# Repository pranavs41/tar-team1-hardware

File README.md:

# TAR Team 1 Hardware

Hardware for the Team 1 swarm mapping project (Texas Aerial Robotics, UT Austin).

## Start here

- **Wiring something to the board, or writing firmware for it:** [`docs/hardware-reference.md`](docs/hardware-reference.md) has every connector, pin, voltage and limit on one page.
- **Reading the schematic without KiCad:** [`schematics/network-drone-fc-schematic.pdf`](schematics/network-drone-fc-schematic.pdf).
- **Designing the frame around the board:** [`cad/network-drone-fc.step`](cad/network-drone-fc.step) is the assembled board as a 3D part.
- **Who is doing what:** [`TASKS.md`](TASKS.md) lists each person's tasks and where their work meets someone else's.
- **What one drone is made of and costs:** [`docs/parts-list.md`](docs/parts-list.md) has every part with its maker, a US or European seller, the price, and the total.

## Repository layout

```
TASKS.md                who owns what, task checklists, the charging concept
pcb/
  network-drone-fc/     KiCad 9 project: the board and the schematic source
    lib/                custom symbols, footprints, 3D models
    production/         gerbers, BOM and notes per board revision
  ground-station/       the ground station's power and main boards (schematics from Python block files)
schematics/             the schematic as a PDF
cad/                    board 3D model (STEP), board pictures, frame CAD
docs/
  hardware-reference.md every connector, pin, voltage and limit on one page
  parts-list.md         every part: maker, seller, price, stock problems, total cost
  charging-board.md     the charging board: plan, parts, and its 7-pin link to the flight controller
  pcb-test-plan.md      how the board gets checked: before ordering, on the bench, in flight
  frame-test-plan.md    load, drop and vibration tests for the printed frame
  DESIGN.md             design doc: requirements, block diagram, parts, power, layout
  circuits/             how every circuit works and why it's there, box by box
  pin-map.md            ESP32 pin, net name and destination, for firmware
  power-budget.md       current per rail, regulator heat, copper and sag check
  bring-up.md           first power-on checklist
  design-decisions.md   dated log of design decisions
  datasheets.md         links to every datasheet and reference design
tools/
  power_budget.py       the model behind power-budget.md
```

KiCad keeps a project's schematic and board in one folder, so both source files are in `pcb/`. The `schematics/` folder holds the readable PDF.

## Network drone flight controller

KiCad 9 project in [`pcb/network-drone-fc/`](pcb/network-drone-fc/). Open `network-drone-fc.kicad_pro`. The design plan is in [`docs/DESIGN.md`](docs/DESIGN.md).

[View the schematic as a PDF](schematics/network-drone-fc-schematic.pdf) or the board pictures in [`cad/`](cad/) if you don't have KiCad. Regenerate the PDF after schematic changes, from the project folder: `kicad-cli sch export pdf network-drone-fc.kicad_sch -o ../../schematics/network-drone-fc-schematic.pdf`.

- 4-layer board, 36 × 39 mm, four 3.2 mm M3 holes on a 20 × 20 mm pattern so it stacks on a bought 20 × 20 4-in-1 ESC
- Two cable ports for off-board parts: J5 carries 5 V and I2C to the TF-Luna obstacle sensor at the front of the drone, J6 carries 5 V and a UART to the VoCore2 networking module
- All parts on the top side except C35, the bulk capacitor on the bottom, so the top can be reflowed on a hot plate and C35 soldered after with an iron; test points (bare pads) are on the bottom
- Designed for a 2S battery only

Where to buy every part, with prices and each maker's country, is in [`docs/parts-list.md`](docs/parts-list.md). The LCSC numbers in the table below are where the KiCad symbols and footprints were imported from; LCSC is a Chinese distributor, and the parts list gives a DigiKey source for each one.

### Parts in `lib/tar_fc`

Symbols, footprints and 3D models (STEP) pulled from LCSC/EasyEDA. The project's library tables already point at them.

| Function | Part | LCSC |
|---|---|---|
| MCU, bare chip (8 MB flash in package) | ESP32-S3FN8 | C2913196 |
| MCU crystal, 40 MHz ±10 ppm | Q22FA12800101 (2016) | C255898 |
| MCU module (fallback only, not used) | ESP32-S3-MINI-1U-N8 | C2980299 |
| Flight IMU (SPI) | ICM-42688-P | C1850418 |
| Barometer | BMP581 | C5362283 |
| GPS | u-blox MAX-M10S | C4153167 |
| Antenna connector (ESP32 / GPS) | U.FL-R-SMT-1 | C88374 |
| 5 V buck (3.8 to 32 V in) | AP63205WU-7 | C2071056 |
| 3.3 V LDO, digital (WSON-6 with thermal pad) | TLV75733PDRVR | C2868428 |
| 3.3 V LDO, sensors (low noise) | TPS7A2033PDBVR | C2862740 |
| Battery TVS (12 V standoff, 2S only) | SMAJ12A | |
| GPS bias-T inductor, 27 nH (fit only for an active antenna) | Murata LQG15HS27NJ02D (0402) | C12669 |
| USB 5 V OR-ing diode | B5819W | C8598 |
| USB ESD | USBLC6-2SC6 | C7519 |
| USB-C (USB 2.0, 16-pin) | TYPE-C 16PIN 2MD(073) | C2765186 |
| ESC connector (8-pin JST-SH) | SM08B-SRSS-TB | C160407 |
| Radio port J6 (4-pin JST-SH, top entry) | BM04B-SRSS-TB | C160390 |
| Bulk capacitor on VBAT (C35, bottom side) | Kyocera AVX TCJD107M025R0055E, 100 µF 25 V polymer tantalum, D case | C2159920 |
| Battery capacitor on the ESC's pads, not on this board | 470 µF 35 V low-ESR electrolytic (any of the ones sold for FPV ESCs) | per build |
| Peripheral port (4-pin JST-GH) | SM04B-GHS-TB (LCSC stock low; drop-in alt XY-SM04B-GHS-TB C51940118) | C189895 |
| VDD3P3 filter inductor, 2.0 nH ±0.1 nH, 900 mA | Murata LQG15HS2N0B02D (0402) | C2986275 |

From the stock KiCad libraries (already have 3D models):

- Passives: `Resistor_SMD` / `Capacitor_SMD` 0402
- Buck inductor, 4.7 µH: `Inductor_SMD:L_1008_2520Metric`. It must have a saturation current of 2 A or more now that the sensor and radio ports draw from the 5 V rail; the FTC252010S4R7MBCA (C5832360) listed earlier saturates near 1.1 A and is no longer enough. Check the value against the AP63205 datasheet.
- 6-pin JST-GH: `Connector_JST:JST_GH_SM06B-GHS-TB_1x06-1MP_P1.25mm_Horizontal`
- Mounting holes: `MountingHole:MountingHole_3.2mm_M3` (plain, no copper, courtyard trimmed to the 3 mm keep-out)
- RESET/BOOT pad pairs: `Jumper:SolderJumper-2_P1.3mm_Open_RoundedPad1.0x1.5mm`

### Adding a part

```
pip install easyeda2kicad
python -m easyeda2kicad --full --lcsc_id=C123456 --output pcb/network-drone-fc/lib/tar_fc
```

Then change the new footprint's `model` path to `${KIPRJMOD}/lib/tar_fc.3dshapes/<name>.step` so it works on every machine.

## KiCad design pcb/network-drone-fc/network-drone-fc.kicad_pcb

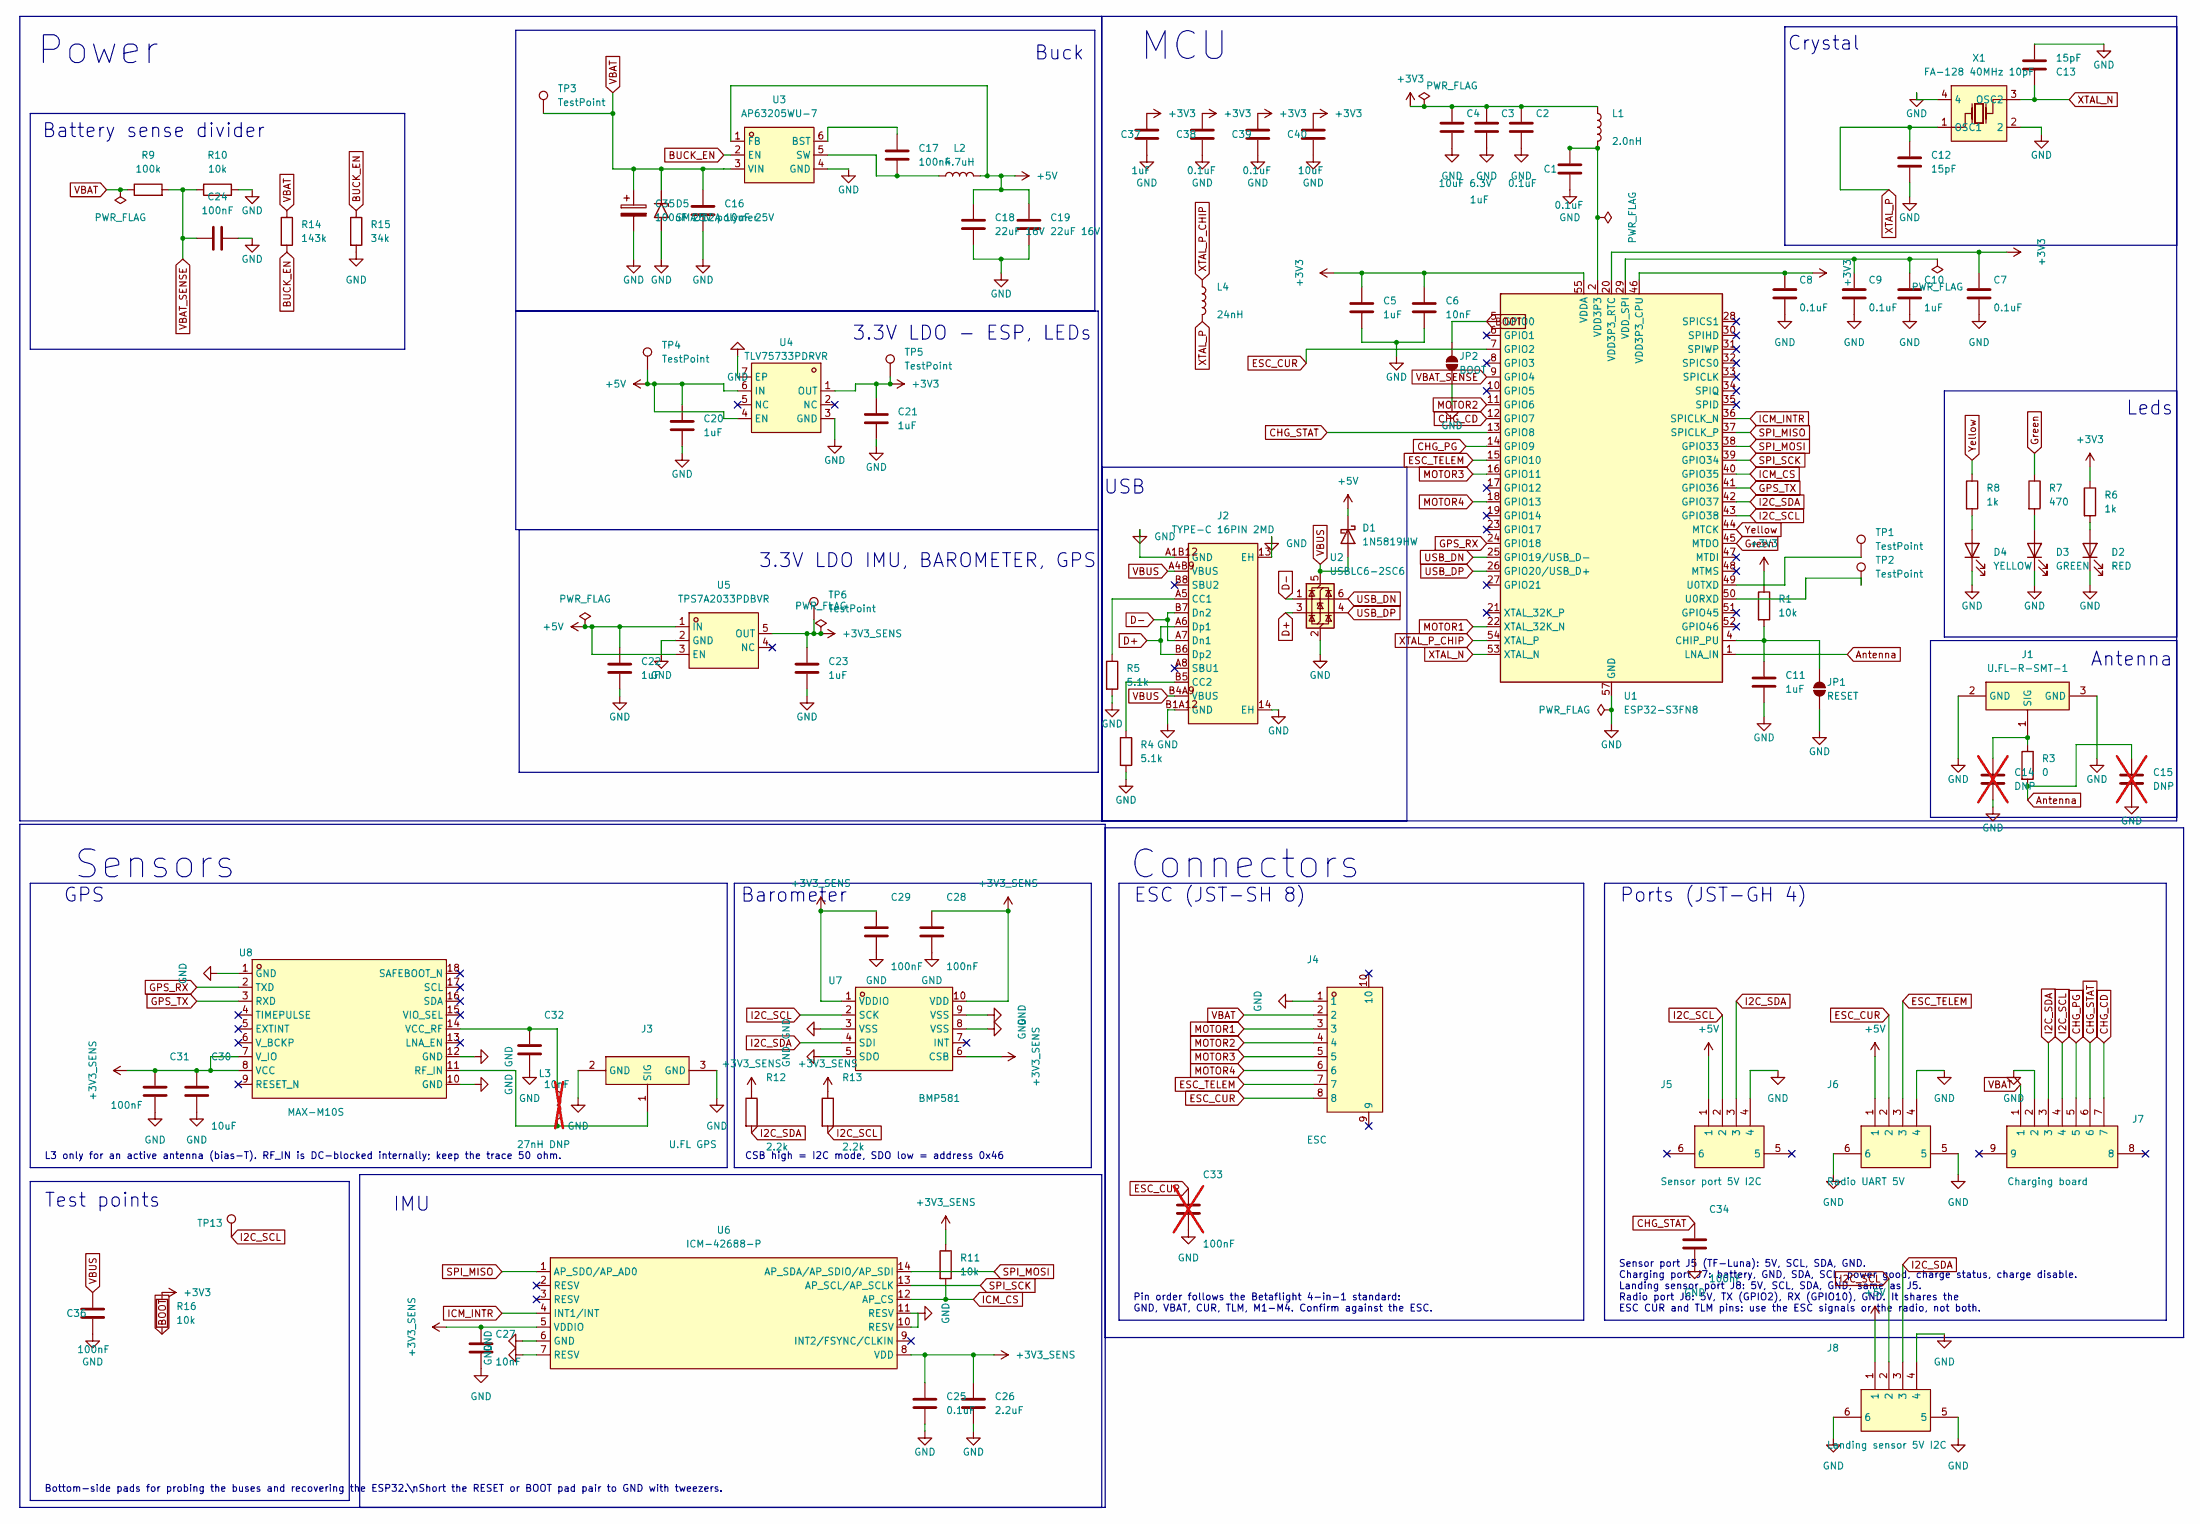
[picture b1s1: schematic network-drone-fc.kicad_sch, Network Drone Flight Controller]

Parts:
C1, C2, C7, C8, C9, C25, C38, C39: 0.1uF; C_0402_1005Metric
C3, C5, C10, C11, C20, C21, C22, C23, C37: 1uF; C_0402_1005Metric
C4: 10uF 6.3V; C_0603_1608Metric
C6, C27, C32: 10nF; C_0402_1005Metric
C12, C13: 15pF; C_0402_1005Metric
C14, C15: DNP; C_0402_1005Metric; not fitted
C16: 10uF 25V; C_0805_2012Metric
C17, C24, C28, C29, C31, C34, C36: 100nF; C_0402_1005Metric
C18, C19: 22uF 16V; C_0805_2012Metric
C26: 2.2uF; C_0402_1005Metric
C30, C40: 10uF; C_0603_1608Metric
C33: 100nF; C_0402_1005Metric; not fitted
C35: 100uF 25V polymer; CP_EIA-7343-31_Kemet-D_HandSolder
D1: 1N5819HW; D_SOD-123
D2: RED; LED_0603_1608Metric
D3: GREEN; LED_0603_1608Metric
D4: YELLOW; LED_0603_1608Metric
D5: SMAJ12A; SMA_L4.4-W2.6-LS5.0-RD
J1: U.FL-R-SMT-1; RF-SMD_FRF05002-JSS103M; MPN U.FL-R-SMT-1(80); LCSC Part C88374
J2: TYPE-C 16PIN 2MD; USB-C-SMD_TYPE-C-16PIN-2MD-073; MPN TYPE-C 16PIN 2MD(073); LCSC Part C2765186
J3: U.FL GPS; RF-SMD_FRF05002-JSS103M; LCSC C88374
J4: ESC; CONN-TH_SM08B-SRSS-TB-LF-SN; LCSC C160407
J5: Sensor port 5V I2C; CONN-SMD_4P-P1.25_SM04B-GHS-TB-LF-SN; LCSC C189895
J6: Radio UART 5V; JST_SH_BM04B-SRSS-TB_1x04_Vertical; LCSC C189895
J7: Charging board; JST_SH_SM07B-SRSS-TB_1x07_Horizontal
J8: Landing sensor 5V I2C; JST_SH_BM04B-SRSS-TB_1x04_Vertical; LCSC C189895
JP1: RESET; SolderJumper-2_P1.3mm_Open_RoundedPad1.0x1.5mm
JP2: BOOT; SolderJumper-2_P1.3mm_Open_RoundedPad1.0x1.5mm
L1: 2.0nH; L_0402_1005Metric
L2: 4.7uH; L_1008_2520Metric
L3: 27nH DNP; L_0402_1005Metric; not fitted
L4: 24nH; L_0402_1005Metric
R1, R10, R11, R16: 10k; R_0402_1005Metric
R3: 0; R_0402_1005Metric
R4, R5: 5.1k; R_0402_1005Metric
R6, R8: 1k; R_0402_1005Metric
R7: 470; R_0402_1005Metric
R9: 100k; R_0402_1005Metric
R12, R13: 2.2k; R_0402_1005Metric
R14: 143k; R_0402_1005Metric
R15: 34k; R_0402_1005Metric
TP1, TP2, TP3, TP4, TP5, TP6, TP13: TestPoint; TestPoint_Pad_D1.0mm
U1: ESP32-S3FN8; QFN-56-1EP_7x7mm_P0.4mm_EP4x4mm
U2: USBLC6-2SC6; SOT-23-6
U3: AP63205WU-7; TSOT-23-6_L2.9-W1.6-P0.95-LS2.8-BL; MPN AP63205WU-7; LCSC Part C2071056
U4: TLV75733PDRVR; TDFN-6_L2.0-W2.0-P0.65-TL-EP; MPN TLV75733PDRVR; LCSC Part C485517
U5: TPS7A2033PDBVR; SOT-23-5_L2.9-W1.6-P0.95-LS2.8-BR; MPN TPS7A2033PDBVR; LCSC Part C2862740
U6: ICM-42688-P; LGA-14_L3.0-W2.5-P0.50-TL; MPN ICM-42688-P; LCSC Part C1850418
U7: BMP581; LGA-10_L2.0-W2.0-P0.50-TL_BMP581; LCSC C5362283
U8: MAX-M10S; SMD-18_L10.1-W9.7-P1.10-TL_SKG09F; LCSC C4153167
X1: FA-128 40MHz 10pF; CRYSTAL-SMD_4P-L2.0-W1.6-BL; MPN Q22FA12800101; LCSC Part C255898

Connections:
+3V3: C2.1, C3.1, C4.1, C5.1, C6.1, C7.1, C8.1, C21.1, C37.1, C38.1, C39.1, C40.1, L1.1, R1.1, R6.1, R16.1, TP5.1, U1.20 (VDD3P3_RTC), U1.46 (VDD3P3_CPU), U1.55 (VDDA), U1.56 (VDDA), U4.1 (OUT)
+3V3_SENS: C23.1, C25.1, C26.2, C27.1, C28.1, C29.1, C30.1, C31.1, R11.1, R12.1, R13.1, TP6.1, U5.5 (OUT), U6.5 (VDDIO), U6.8 (VDD), U7.1 (VDDIO), U7.6 (CSB), U7.10 (VDD), U8.7 (V_IO), U8.8 (VCC)
Antenna: C15.1, R3.2, U1.1 (LNA_IN)
BOOT: JP2.2 (B), R16.2, U1.5 (GPIO0)
BUCK_EN: R14.2, R15.1, U3.2 (EN)
CHG_CD: J7.7, U1.12 (GPIO7)
CHG_PG: J7.5, U1.14 (GPIO9)
CHG_STAT: C34.1, J7.6, U1.13 (GPIO8)
D+: J2.A6 (Dp1), J2.B6 (Dp2), U2.3 (I/O2)
D-: J2.A7 (Dn1), J2.B7 (Dn2), U2.1 (I/O1)
ESC_CUR: C33.1, J4.8, J6.2, U1.7 (GPIO2)
ESC_TELEM: J4.7, J6.3, U1.15 (GPIO10)
GPS_RX: U1.24 (GPIO18), U8.2 (TXD)
GPS_TX: U1.41 (GPIO36), U8.3 (RXD)
Green: R7.1, U1.45 (MTDO)
I2C_SCL: J5.2, J7.4, J8.2, R13.2, TP13.1, U1.43 (GPIO38), U7.2 (SCK)
I2C_SDA: J5.3, J7.3, J8.3, R12.2, U1.42 (GPIO37), U7.4 (SDI)
ICM_CS: R11.2, U1.40 (GPIO35), U6.12 (AP_CS)
ICM_INTR: U1.36 (SPICLK_N), U6.4 (INT1/INT)
MOTOR1: J4.3, U1.22 (XTAL_32K_N)
MOTOR2: J4.4, U1.11 (GPIO6)
MOTOR3: J4.5, U1.16 (GPIO11)
MOTOR4: J4.6, U1.18 (GPIO13)
unnamed: C1.1, L1.2, U1.2 (VDD3P3), U1.3 (VDD3P3)
unnamed: D2.2 (A), R6.2
unnamed: D3.2 (A), R7.2
unnamed: D4.2 (A), R8.2
unnamed: C14.1, J1.1 (SIG), R3.1
unnamed: J2.A5 (CC1), R5.1
unnamed: J2.B5 (CC2), R4.1
unnamed: J3.1 (SIG), L3.2, U8.11 (RF_IN)
unnamed: C11.1, JP1.2 (B), R1.2, U1.4 (CHIP_PU)
unnamed: TP2.1, U1.50 (U0RXD)
unnamed: TP1.1, U1.49 (U0TXD)
unnamed: C9.1, C10.1, U1.29 (VDD_SPI)
unnamed: C17.1, U3.6 (BST)
unnamed: C17.2, L2.1, U3.5 (SW)
unnamed: C32.1, L3.1, U8.14 (VCC_RF)
SPI_MISO: U1.37 (SPICLK_P), U6.1 (AP_SDO/AP_AD0)
SPI_MOSI: U1.38 (GPIO33), U6.14 (AP_SDA/AP_SDIO/AP_SDI)
SPI_SCK: U1.39 (GPIO34), U6.13 (AP_SCL/AP_SCLK)
USB_DN: U1.25 (GPIO19/USB_D-), U2.6 (I/O1)
USB_DP: U1.26 (GPIO20/USB_D+), U2.4 (I/O2)
VBAT: C16.1, C35.1, D5.1 (A1), J4.2, J7.1, R9.1, R14.1, TP3.1, U3.3 (VIN)
VBAT_SENSE: C24.1, R9.2, R10.1, U1.9 (GPIO4)
VBUS: C36.1, D1.2 (A), J2.A4B9 (VBUS), J2.B4A9 (VBUS), U2.5 (VBUS)
XTAL_N: C13.1, U1.53 (XTAL_N), X1.3 (OSC2)
XTAL_P: C12.1, L4.2, X1.1 (OSC1)
XTAL_P_CHIP: L4.1, U1.54 (XTAL_P)
Yellow: R8.1, U1.44 (MTCK)

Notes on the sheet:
Power
Buck
Connectors
USB
Leds
MCU
3.3V LDO IMU, BAROMETER, GPS
3.3V LDO - ESP, LEDs
IMU
Crystal
Antenna
Battery sense divider
Sensors
Barometer
CSB high = I2C mode, SDO low = address 0x46
GPS
L3 only for an active antenna (bias-T). RF_IN is DC-blocked internally; keep the trace 50 ohm.
ESC (JST-SH 8)
Pin order follows the Betaflight 4-in-1 standard: GND, VBAT, CUR, TLM, M1-M4. Confirm against the ESC.
Ports (JST-GH 4)
Sensor port J5 (TF-Luna): 5V, SCL, SDA, GND. Charging port J7: battery, GND, SDA, SCL, power good, charge status, charge disable. Landing sensor port J8: 5V, SCL, SDA, GND, same as J5. Radio port J6: 5V, TX (GPIO2), RX (GPIO10), GND. It shares the ESC CUR and TLM pins: use the ESC signals or the ra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
Test points
Bottom-side pads for probing the buses and recovering the ESP32.\nShort the RESET or BOOT pad pair to GND with tweezers.

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
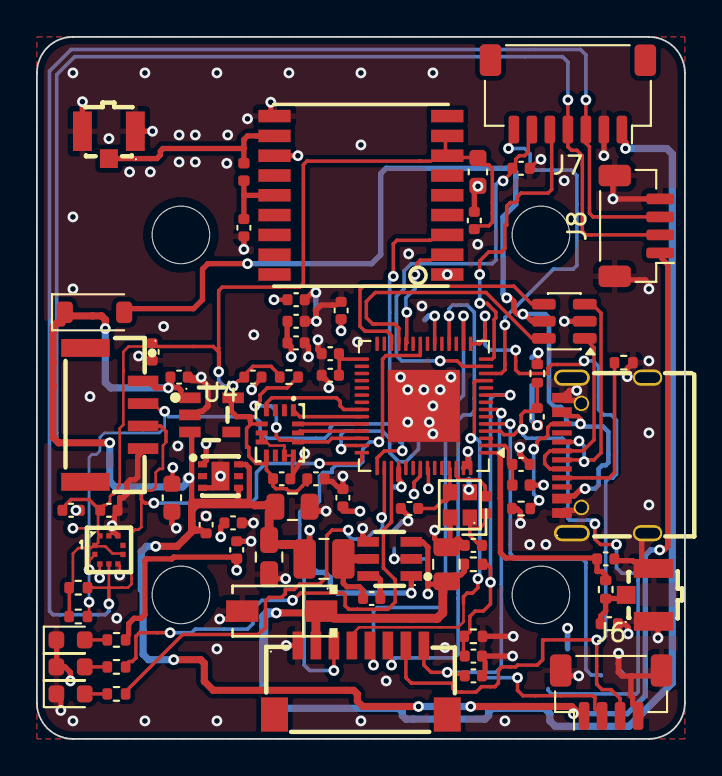
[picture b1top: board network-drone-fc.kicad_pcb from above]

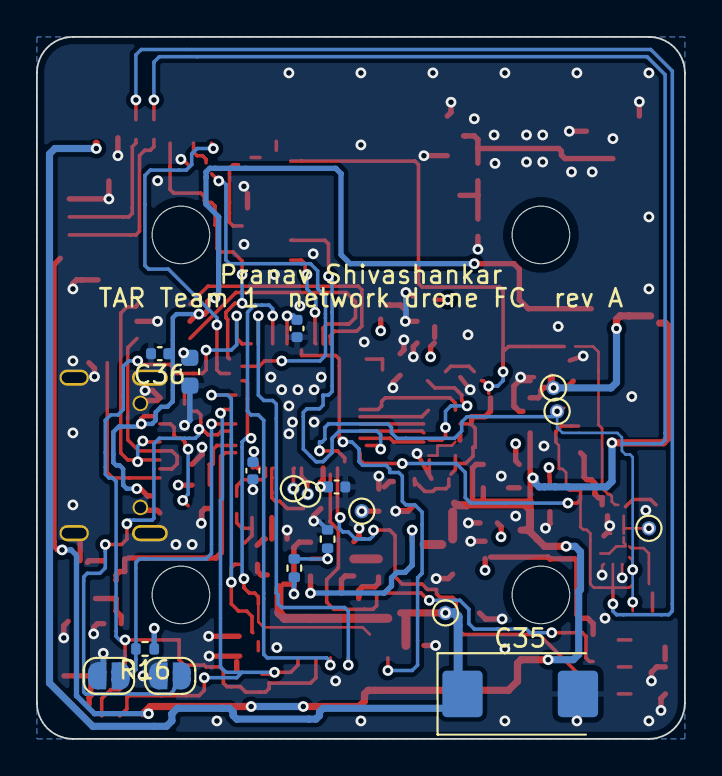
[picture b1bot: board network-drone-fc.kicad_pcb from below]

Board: 4 copper layers, 36.0 x 39.0 mm, 94 parts (18 on the bottom side), 52 nets.

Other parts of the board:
H1, H2, H3, H4: MountingHole_3.2mm_M3

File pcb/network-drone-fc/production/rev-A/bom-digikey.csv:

Quantity,Manufacturer Part Number,Manufacturer,Customer Reference,Description,Per board,Unit price USD (2026-10-11)
1,ESP32-S3FN8,Espressif,U1,ESP32-S3 processor,1,4.17
1,MAX-M10S-00B,u-blox,U8,GPS module,1,11.42
1,BMP581,Bosch Sensortec,U7,Barometer,1,3.35
1,TLV75733PDRVR,Texas Instruments,U4,"3.3 V regulator, 1 A",1,0.48
1,USBLC6-2SC6,STMicroelectronics,U2,USB protection,1,0.54
1,FA-128 40.0000MF10Z-K3,Epson,X1,"40 MHz crystal, 10 pF, ±10 ppm",1,1.11
1,TCJD107M025R0055,Kyocera AVX,C35,100 µF 25 V polymer capacitor,1,3.65
1,SMAJ12A,Littelfuse,D5,Battery surge diode,1,0.51
1,1N5819HW-7-F,Diodes Incorporated,D1,"Schottky diode, 1 A 40 V, SOD-123",1,0.31
3,150060RS75000,Würth Elektronik,D2,"LED 0603, red",1,0.15
3,150060VS75000,Würth Elektronik,D3,"LED 0603, yellow-green",1,0.15
3,150060YS75000,Würth Elektronik,D4,"LED 0603, yellow",1,0.15
1,SM08B-SRSS-TB,JST,J4,"ESC connector, JST-SH 8-pin",1,0.85
1,SM07B-SRSS-TB,JST,J7,"Charging port, JST-SH 7-pin",1,0.80
2,BM04B-SRSS-TB,JST,"J6, J8","Radio port and landing sensor port, JST-SH 4-pin top entry",2,0.53
2,U.FL-R-SMT-1(10),Hirose,"J1, J3","Antenna sockets, U.FL",2,1.67
1,USB4105-GF-A,GCT,J2,"USB-C socket, 16-pin",1,0.80
1,CIGW252010EH4R7MNE,Samsung Electro-Mechanics,L2,"Buck inductor, 4.7 µH, 2.2 A saturation",1,0.29
10,LQG15HS2N0B02D,Murata,L1,"Radio supply inductor, 2.0 nH",1,0.10
10,LQW15AN24NG00D,Murata,L4,"Crystal line inductor, 24 nH",1,0.12
20,GRM155R71C104KA88J,Murata,"C1, C2, C7 to C9, C17, C24, C25, C28, C29, C31, C34, C36, C38, C39","0.1 µF 16 V, 0402",15,0.10
10,CL05A105KP5NNNC,Samsung Electro-Mechanics,"C3, C5, C10, C11, C20 to C23, C37","1 µF 10 V, 0402",9,0.10
10,GRM155R71H103KA88D,Murata,"C6, C27, C32","10 nF 50 V, 0402",3,0.10
10,GRM1555C1H150JA01D,Murata,"C12, C13","15 pF 50 V, 0402",2,0.10
10,GRM155R61C225KE11J,Murata,C26,"2.2 µF 16 V, 0402",1,0.22
10,GRM188R60J106ME47D,Murata,"C4, C30, C40","10 µF 6.3 V, 0603",3,0.12
10,GRM21BR61C226ME44L,Murata,"C18, C19","22 µF 10 V, 0805",2,0.19
1,C2012X5R1E106K125AB,TDK,C16,"10 µF 25 V, 0805",1,0.34
10,RC0402FR-0710KL,Yageo,"R1, R10, R11, R16","10 kΩ 1%, 0402",4,0.10
10,RC0402FR-075K1L,Yageo,"R4, R5","5.1 kΩ 1%, 0402",2,0.10
10,RC0402FR-071KL,Yageo,"R6, R8","1 kΩ 1%, 0402",2,0.10
10,RC0402FR-072K2L,Yageo,"R12, R13","2.2 kΩ 1%, 0402",2,0.10
10,RC0402FR-07470RL,Yageo,R7,"470 Ω 1%, 0402",1,0.10
10,RC0402FR-07100KL,Yageo,R9,"100 kΩ 1%, 0402",1,0.10
10,RC0402FR-07143KL,Yageo,R14,"143 kΩ 1%, 0402",1,0.10
10,RC0402FR-0734KL,Yageo,R15,"34 kΩ 1%, 0402",1,0.10
10,RC0402JR-070RL,Yageo,R3,"0 Ω link, 0402",1,0.10
